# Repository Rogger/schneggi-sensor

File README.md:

# Schneggi sensor 🐌 
A Zigbee sensor integrated with Home Assistant for monitoring temperature, humidity, and optional CO2.

- High accuracy temperature and humidity measurements ([Sensirion SHTC3](https://www.sensirion.com/products/catalog/SHTC3/))
- High accuracy CO2 measurement ([Sensirion SCD40](https://sensirion.com/products/catalog/SCD40)) - optional board
  - CO2 firmware exposes two temperatures: SHTC3 ambient temperature on endpoint 1
    and SCD40 temperature on endpoint 2. The SCD40 reading uses the same sample as
    CO2 and can be affected by self-heating and enclosure conditions; use SHTC3
    as the primary ambient reading. The existing SHTC3 humidity entity is unchanged.
- Low power consumption and long battery life for the non-CO2 variant
  - Hardware: nRF52840 chip, low-current linear regulator, battery monitor with on/off capability 
  - Software: Zigbee sleepy end device for the non-CO2 variant
  - Measured: 3uA average over 1 minute without CO2 (before OTA support)
- The non-CO2 variant can be powered with 3V to 6V (JST connector), e.g. 350mAh li-poly.
- The CO2 variant is USB-C powered. It advertises DC power, keeps its Zigbee receiver on while idle, and does not report a battery.
- Small footprint (3,5cm x 3cm )
- Tested with [Home Assistant](https://www.home-assistant.io/) and [SkyConnect](https://www.home-assistant.io/skyconnect/)

After upgrading CO2 firmware to a build with the second temperature endpoint,
Home Assistant ZHA must discover endpoint 2. Re-interview/reconfigure the device;
if the endpoint list remains cached, remove and pair the device again. Both
temperature entities use the standard Temperature Measurement cluster, so no
custom quirk is required. You can rename them in HA to **Temperature SHTC3** and
**Temperature SCD40**; endpoint 1 is SHTC3 and endpoint 2 is SCD40. The new reading
uses the same sampling interval, 0.1 °C fallback change threshold, daily refresh,
and standard Configure Reporting support as the existing temperature reading.

## Battery power management

The non-CO2 debug and production profiles enable I2C runtime power management.
The application enables it on the sensor bus; the TWIM driver suspends the
controller and applies its sleep pin configuration between transfers.
Polling, sampling intervals, and SHTC3 measurement accuracy are unchanged.

Failed SHTC3 fetches attempt a sleep command after a 13 ms settling delay,
working around the SDK driver's missing error-path cleanup without changing
the shared SDK. Cleanup is best-effort: an inaccessible sensor cannot be forced
to sleep. The original fetch error is retained and no failed sample is reported.
The command and conversion timing follow the
[SHTC3 datasheet](https://sensirion.com/file/datasheet_shtc3).

Battery-profile rejoin delays grow from 1 second exponentially to a one-hour
cap (1, 2, 4, ..., 1024, 2048, 3600 seconds). Successful reconnection resets the
backoff. After prolonged outages, recovery may therefore wait up to an hour
before the next attempt, plus commissioning time. USB-powered CO2 profiles keep
their 15-minute cap and do not enable I2C runtime PM or battery monitoring.

Battery measurements run hourly in debug builds and daily in production builds.
If sampling or updating either battery attribute fails, the firmware retries on
the next sensor cycle (one or ten minutes respectively). A successful update
starts the next battery interval. The firmware attempts to disable the divider
on every path and logs cleanup failures.

The firmware restarts if Zigbee startup or scheduling a required measurement,
rejoin, or watchdog alarm fails, so it cannot stay running indefinitely without
that work. Ordinary join failures still use the rejoin backoff described above.
Alarm replacement removes previous instances and uses overflow-safe conversion
for the full supported sampling range of 1–1440 minutes. Repeated Identify
requests keep one blink alarm; scheduling failure stops the LED animation.

Validate on hardware before relying on battery-life estimates: compare at least
an hour of production-profile current capture before/after, with the debugger
disconnected; check repeated sensor reads, transient I2C failures, and recovery
after a prolonged coordinator outage. Host tests cannot verify physical sleep
current or bus suspend/resume behavior.

## Zigbee reporting

ZHA can configure the standard minimum interval, maximum interval, and
reportable change for endpoint 1's Temperature Measurement (`0x0402`) and
Relative Humidity Measurement (`0x0405`) measured-value (`0x0000`) attributes.
Their changes are in hundredths of a degree Celsius and hundredths of a percent
relative humidity. For settings that differ from ZBOSS's defaults, ZBOSS applies
them to every new sensor reading. Without a configuration, or after reporting
is restored to defaults, the firmware retains its 0.1 °C / 1% change thresholds
and 24-hour refresh. A request for ZBOSS's exact default settings (5-second
minimum, no periodic maximum, zero change) is indistinguishable from a reset
and also uses the firmware fallback.

The CO2 Concentration Measurement (`0x040D`) measured value is refreshed on
every sample, so its Zigbee minimum and maximum reporting intervals can be
configured. ZBOSS treats the single-precision CO2 value as a
changed/unchanged attribute and does not apply a numeric reportable-change
threshold to it. The sensor still samples every minute in debug builds and
every ten minutes in production builds; configuring a shorter reporting
interval does not produce a newer measurement.

## PCB
The PCB was designed with KiCad 7 and manufactured/assembled with JLCPCB. All relevant files can be found in the [repo](hardware)

## HomeAssistant

## Case

## Build
This project uses a **west workspace** (manifest in `west.yml`) and a local Makefile wrapper.
The supported stack is **nRF Connect SDK 3.4.1** with **Zigbee R23 add-on 1.4.0**,
using its R22 behavior mode. SDK and add-on revisions are pinned in `west.yml`;
Zephyr, MCUboot, and other modules come from the SDK manifest. The SCD40 uses
Zephyr's native SCD4X driver. See [migration notes](docs/sdk-upgrade.md).

### 1) One-time workspace setup
Install Nordic's `nrfutil` and the matching toolchain (the Makefile selects the
toolchain associated with this release, rather than the first installed bundle):

```bash
nrfutil install toolchain-manager device
nrfutil toolchain-manager install --ncs-version v3.4.1 --install-dir "$HOME/ncs"
```

From the project directory, initialize the workspace if it does not already exist:

```bash
nrfutil toolchain-manager launch --ncs-version v3.4.1 --install-dir "$HOME/ncs" -- west init -l .
make west-update
```

This initializes a west workspace in the parent directory and fetches all required modules.
For an existing workspace, run `make west-update` with the new toolchain.

The Makefile uses the parent west workspace when `../.west` exists. To use a
different NCS workspace, pass `NCS_WORKSPACE=/path/to/workspace`, or put this
override in the ignored `local.mk`. That workspace must use this checkout's
`west.yml`, including the Zigbee add-on. Builds reject mismatched manifests and
module revisions. An SDK workspace initialized from Nordic's manifest alone
does not include Schneggi's pinned add-on.
Builds compare the cached sysbuild source with the selected NCS workspace and
regenerate incompatible project build directories automatically. West's
automatic pristine mode handles other cache incompatibilities.

### 2) Build
Firmware builds now include signed MCUboot/Zigbee OTA support. Supply
`OTA_SIGNING_KEY=/absolute/private/schneggi.pem` to the build commands below.
For development only, use `OTA_ALLOW_TEST_KEY=ON` to opt into the public SDK key.
See [OTA setup, signing, ZHA configuration, and recovery](docs/ota.md).
Interrupted transfers can resume from the last completed 4 KiB flash page after
retrying Install in Home Assistant, including after a sensor power cycle. The
running firmware must already include resume support.

```bash
cd <project-dir>
make build-debug OTA_ALLOW_TEST_KEY=ON
```

Default output:
- `build_debug/merged.hex`
- `build_debug/schneggi-sensor/zephyr/zephyr.elf`

### Build Profiles

Convenience targets:

- `make build-debug`
  - Debug build without CO2 / SCD4X
- `make build-debug-co2`
  - Debug build with CO2 / SCD4X
- `make build-production`
  - Production build without CO2 / SCD4X
- `make build-production-co2`
  - Production build with CO2 / SCD4X

Equivalent flash targets:

```bash
make flash-debug
make flash-debug-co2
make flash-production
make flash-production-co2
```

For the CO2 production firmware:

```bash
make build-production-co2 OTA_SIGNING_KEY=/absolute/private/schneggi.pem
make flash-production-co2
```

### 3) Test (host unit tests)

```bash
make test
```

The host tests cover reporting thresholds and counter wraparound, battery conversion,
CO2 attribute validation, Zigbee signal handling, OTA behavior for both power profiles,
and rejoin retry/cancellation behavior. They also exercise sensor fetch/read failures,
failed attribute writes, custom reporting and resets, exact fixed-point conversion,
battery ADC/GPIO error cleanup and retry timing, and OTA package validation/index updates.
OTA resume tests simulate resets throughout a download, torn flash writes and
checkpoint commits, corrupted saved data, and maximum-size images.
Runtime tests cover failed startup, alarm exhaustion, cancellation failures,
duplicate reconnect signals, and long scheduling intervals. The Python suite also
checks that PCB rule-check failures prevent manufacturing exports under parallel make.
CI runs them in Debug and Release and builds all four firmware profiles. ADC/GPIO
behavior, network recovery over the radio, and sleep current still require hardware tests.

Version tags also run the [GitHub release workflow](docs/releases.md), which publishes
clearly labeled public-development-key firmware, a ready-to-copy ZHA OTA ZIP,
and checksums after validation. Releases preserve the separate CO2/non-CO2 firmware versions.

`make clean` accepts only `build` or `build_*` directories inside this project.

### 4) Flash

Flash targets use `nrfutil device`, which requires SEGGER J-Link on the host.
Programming erases only flash sectors touched by the firmware, verifies the
result, and resets the sensor. `make erase` still erases the entire chip.

```bash
make flash-debug
```

For a specific J-Link probe:

```bash
make flash-production-co2 SNR=<your_jlink_serial>
```

### Useful overrides

```bash
make build BUILD_DIR=build_custom
make build CONF_FILE=prj_production_no_scd4x.conf OVERLAY='boards/schneggi_sensor.overlay;boards/no_scd4x.overlay'
make build-production-co2 NCS_WORKSPACE=/path/to/workspace
make flash SNR=<your_jlink_serial>
```

### Keep dependencies in sync
After updating `west.yml`:

```bash
make west-update
```

## Resources
- The PCB design was inspired by [Getting Started With nRF52 MCU in a PCB](https://resources.altium.com/p/getting-started-nrf52-mcu-pcb#getting-started-schematics)
- The repos [zigbee-plant-sensor](https://github.com/stanvn/zigbee-plant-sensor) and [b-parasite](https://github.com/rbaron/b-parasite) are a great start
- The [Zephyr SCD4X driver](https://github.com/nrfconnect/sdk-zephyr/tree/ncs-v3.4.1/drivers/sensor/sensirion/scd4x)
- The [nRF Sniffer](https://developer.nordicsemi.com/nRF_Connect_SDK/doc/latest/nrf/protocols/zigbee/tools.html) with [https://www.wireshark.org](Wireshark) is a helpful tool to debug Zigbee communication
- The [ZigBee specification 22 1.0](https://csa-iot.org/wp-content/uploads/2022/01/docs-05-3474-22-0csg-zigbee-specification-1.pdf) and [ZigBee Cluster Library R8](https://zigbeealliance.org/wp-content/uploads/2021/10/07-5123-08-Zigbee-Cluster-Library.pdf)

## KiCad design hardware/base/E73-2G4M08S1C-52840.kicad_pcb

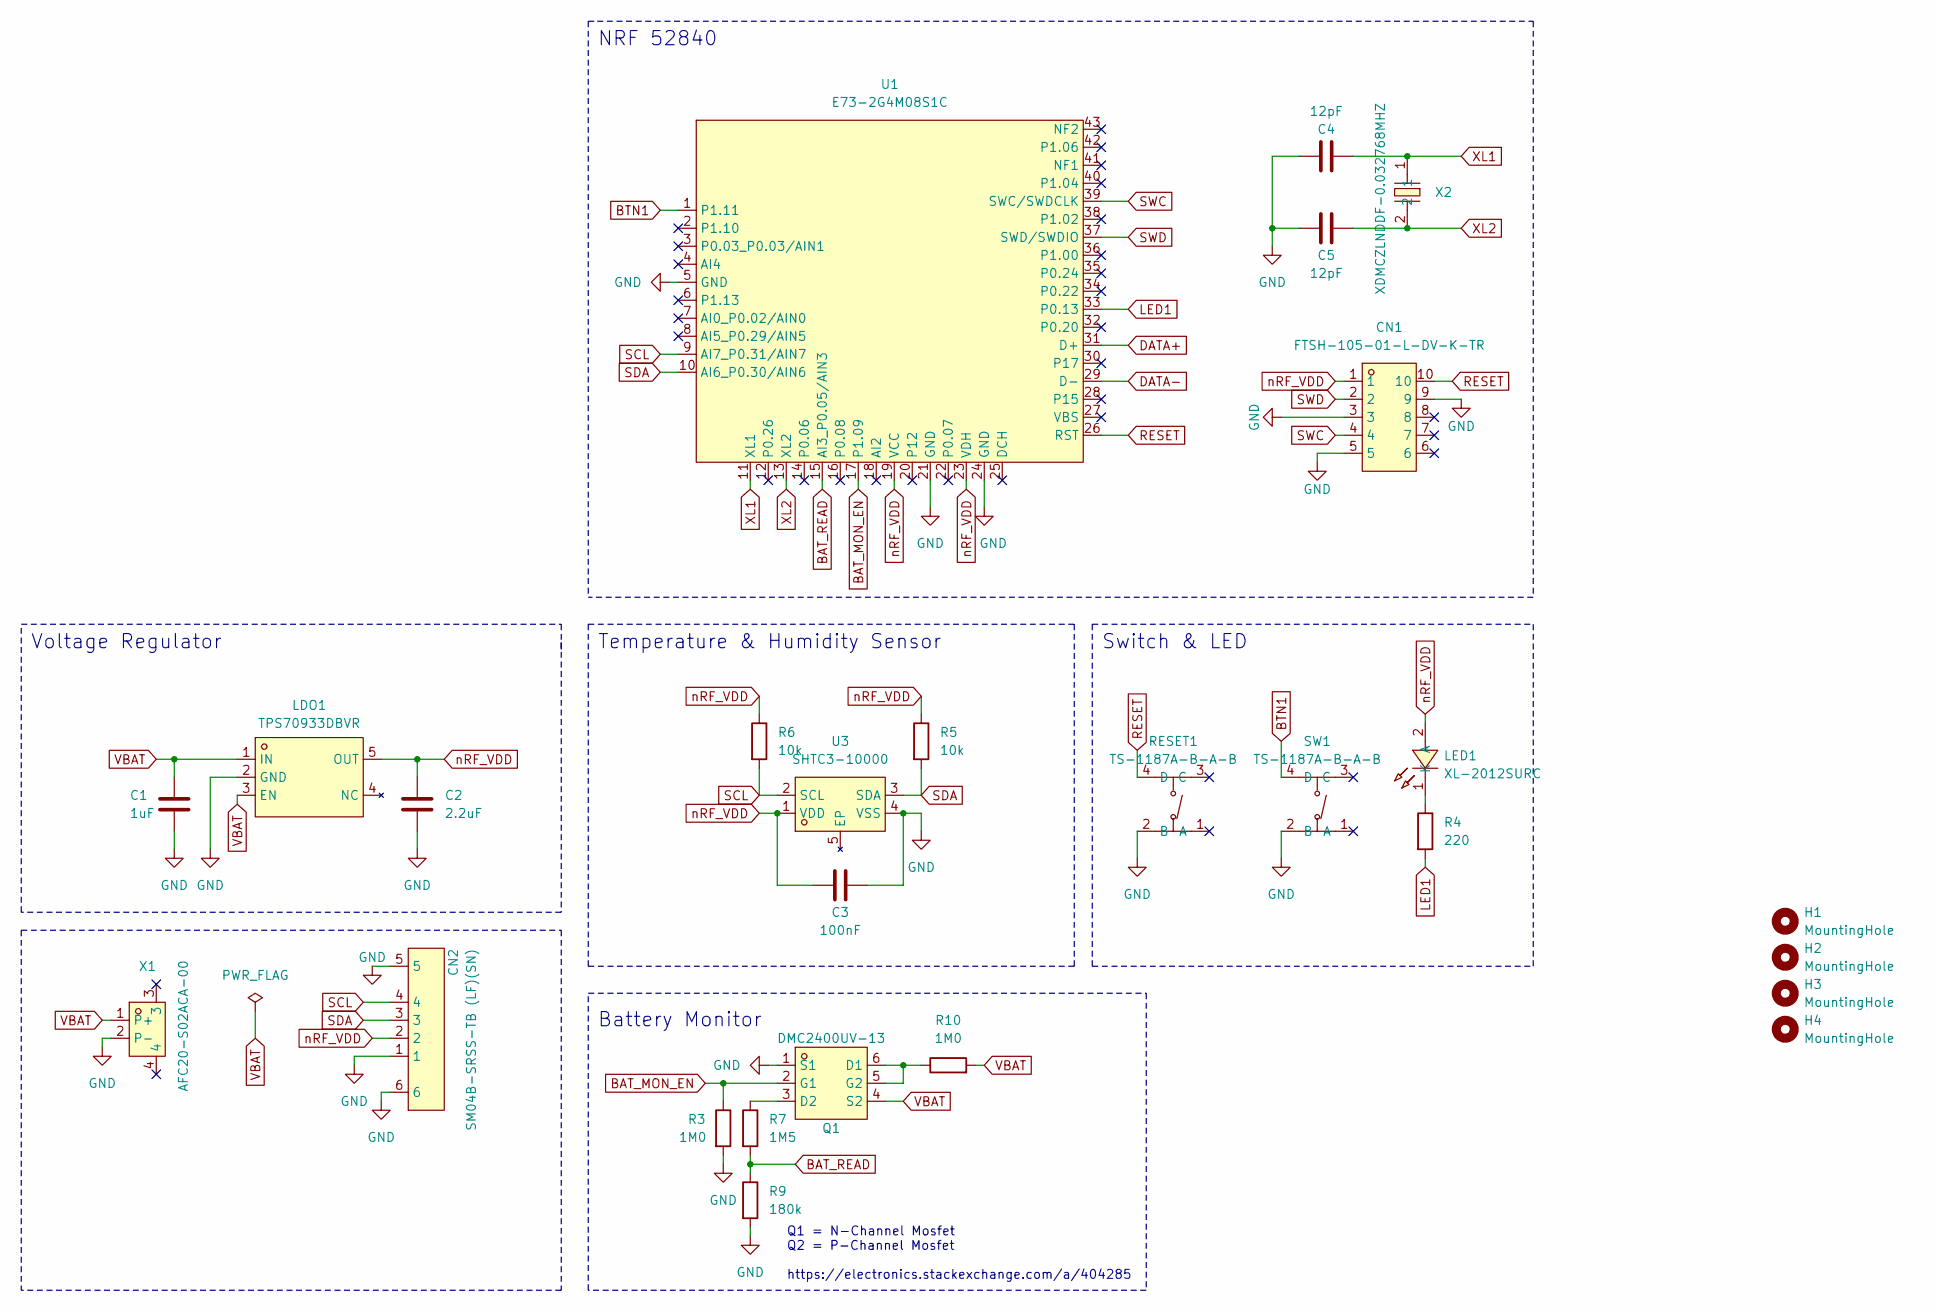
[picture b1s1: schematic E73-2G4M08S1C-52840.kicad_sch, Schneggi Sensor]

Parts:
C1: 1uF; C_0603_1608Metric; LCSC C15849
C2: 2.2uF; C_0603_1608Metric; LCSC C23630
C3: 100nF; C_0603_1608Metric; LCSC C14663
C4, C5: 12pF; C_0603_1608Metric; LCSC C38523
CN1: FTSH-105-01-L-DV-K-TR; CONN-SMD_FTSH-105-01-L-DV-K-TR; LCSC Part C448647
CN2: SM04B-SRSS-TB (LF)(SN); CONN-SMD_4P-P1.00_SM04B-SRSS-TB-LF-SN; LCSC Part C160404
H1, H2, H3, H4: MountingHole; MountingHole_2.2mm_M2
LDO1: TPS70933DBVR; SOT-23-5_L3.0-W1.7-P0.95-LS2.8-BR; LCSC Part C89347
LED1: XL-2012SURC; LED0805-RD_RED; LCSC C84256
Q1: DMC2400UV-13; SOT-563_L1.6-W1.2-P0.50-LS1.6-BL; LCSC Part C500791
R3, R10: 1M0; R_0603_1608Metric; LCSC C22935
R4: 220; R_0603_1608Metric; LCSC C22962
R5, R6: 10k; R_0603_1608Metric; lcsc C98220
R7: 1M5; R_0603_1608Metric; LCSC C4172
R9: 180k; R_0603_1608Metric; LCSC C22827
RESET1: TS-1187A-B-A-B; SW-SMD_4P-L5.1-W5.1-P3.70-LS6.5-TL-2; LCSC Part C318884
SW1: TS-1187A-B-A-B; SW-SMD_4P-L5.1-W5.1-P3.70-LS6.5-TL-2; LCSC Part C318884
U1: E73-2G4M08S1C; WIRELM-SMD_E73-2G4M08S1C; LCSC Part C356849
U3: SHTC3-10000; DFN-4_L2.0-W2.0-P1.00-BL-EP; LCSC Part C2880044
X1: AFC20-S02ACA-00; CONN-SMD_AFC20-S02ACA-00; LCSC Part C2764211
X2: XDMCZLNDDF-0.032768MHZ; CRYSTAL-SMD_L3.2-W1.5-1; LCSC Part C32346

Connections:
BAT_MON_EN: Q1.2 (G1), R3.1, U1.17 (P1.09)
BAT_READ: R7.2, R9.1, U1.15 (AI3_P0.05/AIN3)
BTN1: SW1.4 (D), U1.1 (P1.11)
DATA+: U1.31 (D+)
DATA-: U1.29 (D-)
GND: C1.2, C2.2, C3.2, C4.1, C5.1, CN1.3, CN1.5, CN1.9, CN2.1, CN2.5, CN2.6, LDO1.2 (GND), Q1.1 (S1), R3.2, R9.2, RESET1.2 (B), SW1.2 (B), U1.5 (GND), U1.21 (GND), U1.24 (GND), U3.4 (VSS), X1.2 (P-)
LED1: R4.2, U1.33 (P0.13)
unnamed: LED1.1 (K), R4.1
unnamed: Q1.5 (G2), Q1.6 (D1), R10.1
unnamed: Q1.3 (D2), R7.1
RESET: CN1.10, RESET1.4 (D), U1.26 (RST)
SCL: CN2.4, R6.2, U1.9 (AI7_P0.31/AIN7), U3.2 (SCL)
SDA: CN2.3, R5.2, U1.10 (AI6_P0.30/AIN6), U3.3 (SDA)
SWC: CN1.4, U1.39 (SWC/SWDCLK)
SWD: CN1.2, U1.37 (SWD/SWDIO)
VBAT: C1.1, LDO1.1 (IN), LDO1.3 (EN), Q1.4 (S2), R10.2, X1.1 (P+)
XL1: C4.2, U1.11 (XL1), X2.1
XL2: C5.2, U1.13 (XL2), X2.2
nRF_VDD: C2.1, C3.1, CN1.1, CN2.2, LDO1.5 (OUT), LED1.2 (A), R5.1, R6.1, U1.19 (VCC), U1.23 (VDH), U3.1 (VDD)

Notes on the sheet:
Q1 = N-Channel Mosfet Q2 = P-Channel Mosfet https://electronics.stackexchange.com/a/404285
Temperature & Humidity Sensor
Switch & LED
Voltage Regulator
Battery Monitor
NRF 52840

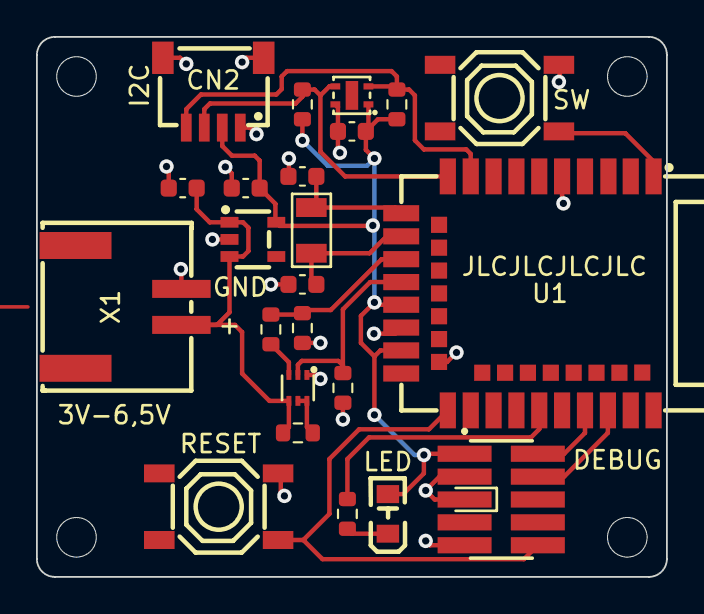
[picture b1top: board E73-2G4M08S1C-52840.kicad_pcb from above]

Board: 2 copper layers, 35.0 x 30.0 mm, 27 parts (0 on the bottom side), 17 nets.

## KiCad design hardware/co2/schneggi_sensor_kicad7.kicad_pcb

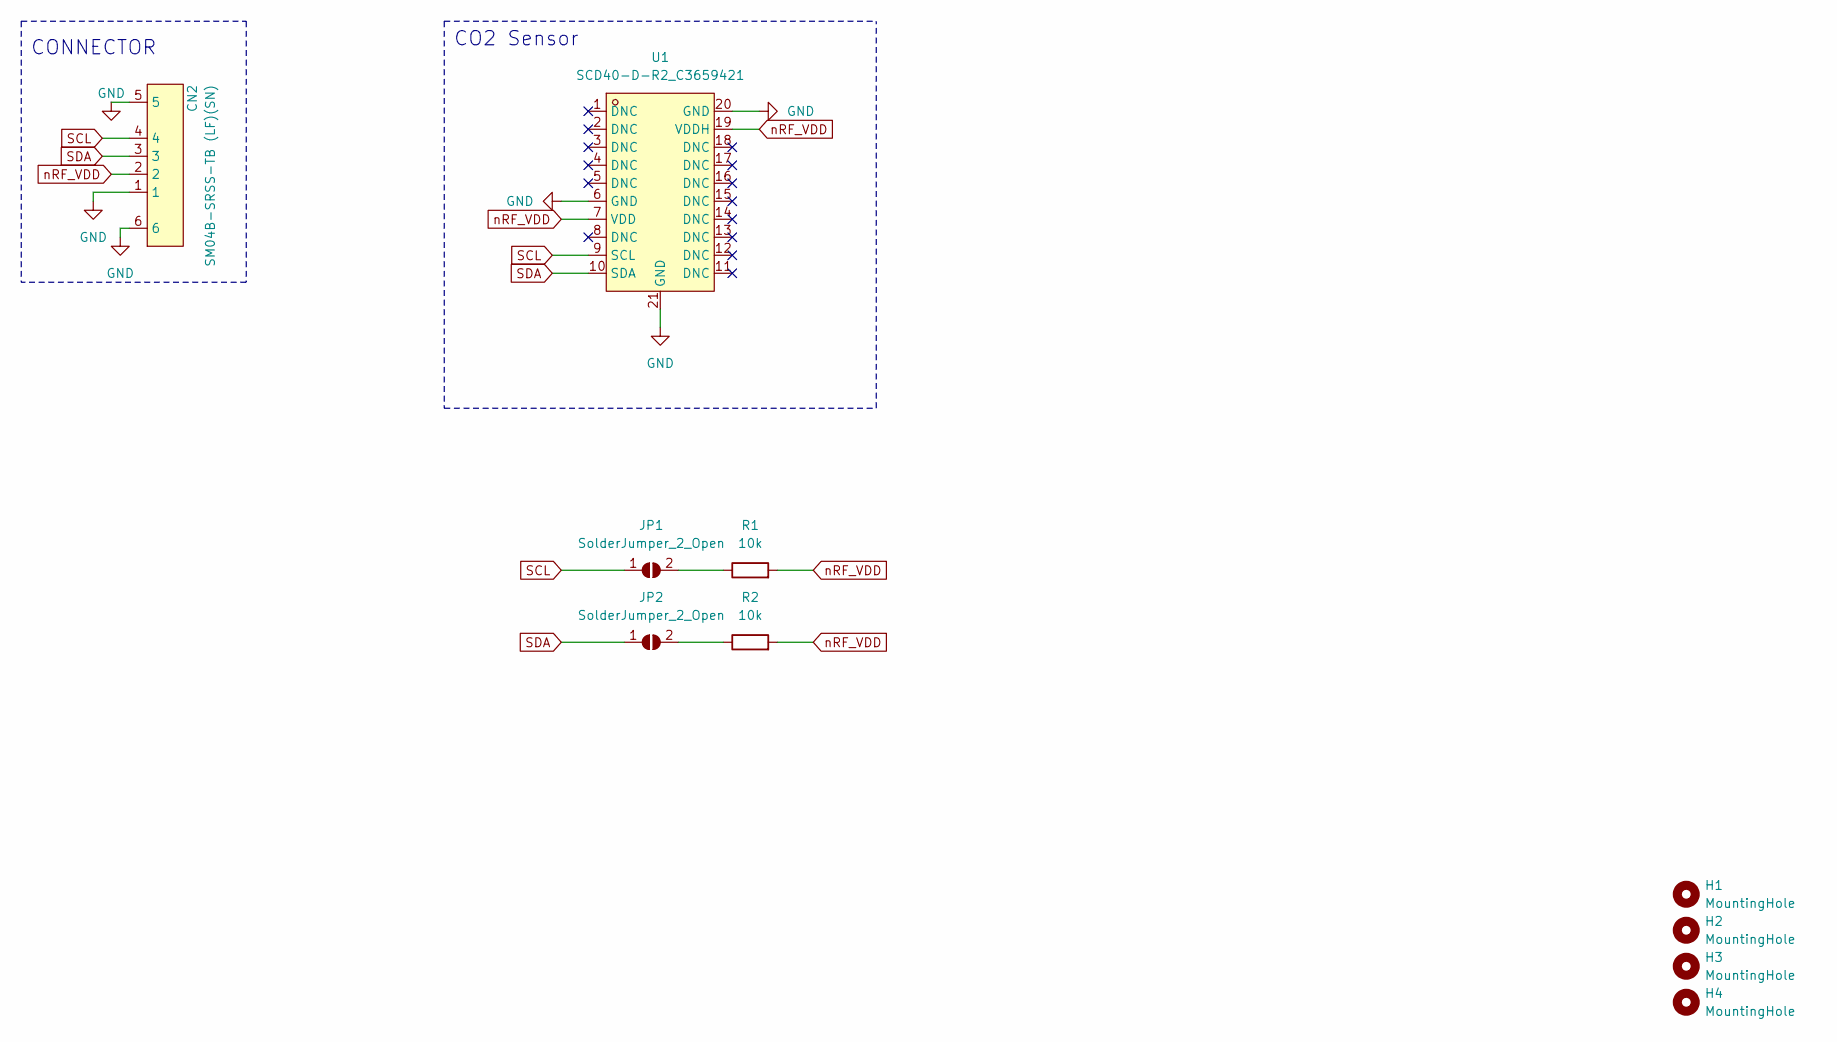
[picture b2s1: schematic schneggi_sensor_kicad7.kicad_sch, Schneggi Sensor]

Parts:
CN2: SM04B-SRSS-TB (LF)(SN); CONN-SMD_4P-P1.00_SM04B-SRSS-TB-LF-SN; LCSC Part C160404
H1, H2, H3, H4: MountingHole; MountingHole_2.2mm_M2
JP1, JP2: SolderJumper_2_Open; SolderJumper-2_P1.3mm_Open_TrianglePad1.0x1.5mm
R1, R2: 10k; R_0603_1608Metric
U1: SCD40-D-R2_C3659421; LGA-20_L10.1-W10.1-P1.25-TL; LCSC Part C3659421

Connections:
GND: CN2.1, CN2.5, CN2.6, U1.6 (GND), U1.20 (GND), U1.21 (GND)
unnamed: JP1.2 (B), R1.1
unnamed: JP2.2 (B), R2.1
SCL: CN2.4, JP1.1 (A), U1.9 (SCL)
SDA: CN2.3, JP2.1 (A), U1.10 (SDA)
nRF_VDD: CN2.2, R1.2, R2.2, U1.7 (VDD), U1.19 (VDDH)

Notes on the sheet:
CO2 Sensor
CONNECTOR

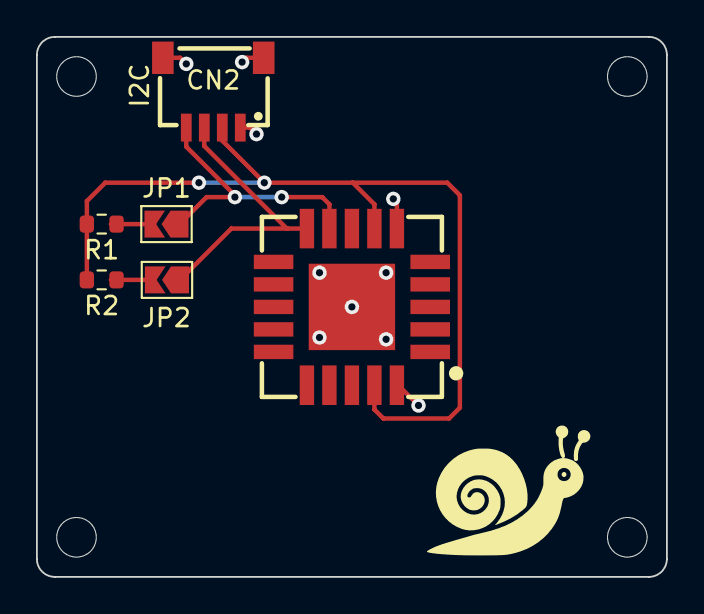
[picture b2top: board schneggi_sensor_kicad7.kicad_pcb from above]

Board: 2 copper layers, 35.0 x 30.0 mm, 10 parts (0 on the bottom side), 6 nets.

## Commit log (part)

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2023-11-21 Initial version
2023-11-21 Add schema pdf
2023-11-21 Fix images in readme
2023-11-21 Optimize for battery life
2023-11-30 Lower power consumption
2023-12-19 Long Poll, Transmit Power
2023-12-20 Fix ZigBee known issue
2024-02-09 Custom Memory, Sleepy End Device
2024-02-09 Set Q size to 128, long poll to 60s, schedule sensor loop after zigbee is intialized
2024-02-16 Remove PWM, Disable UART
2024-02-18 Update README.md for power consumption
2024-07-31 Add CO2 support
2024-07-31 --amend
2024-08-09 Thread status
2024-08-16 Progress
2024-08-16 formatting
2024-08-17 Debug
2024-08-18 Add CI
2024-08-18 Implement zboss handler
2024-08-18 Cleanup
2024-08-29 Add hardware files
2024-08-29 Add V1.1 with CO2 support (#2)
    V1.1
    Smaller outline
    Remove USB-C and physical switch
    Improve signal strength
    Add PH connector for additional sensor boards
    Add CO2 board
2024-09-15 nrf sdk 2.5.2
2024-10-05 Improve broken rejoin
2024-10-05 Add status badge
2024-10-05 Add Kicad files
2024-10-05 Clean
2024-10-05 Add Kicad files for 1.1 (#4)
2024-10-05 Improve broken rejoin (#3)
2025-01-31 Add case stl file
2025-01-31 Add stl files
2025-01-31 Add new Case (#5)
2025-03-22 Add exponetial backoff
2025-06-30 refactor: improve battery level calculation
    The previous implementation of the battery level calculation was inefficient and prone to errors. This commit refactors the `battery_level_pptt` function to use a more robust and efficient algorithm.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
2026-02-08 Fix sensor runtime bugs and concentration cluster typing
2026-02-08 Harden sensor loop and commissioning runtime logic
2026-02-08 Add return-code checks for GPIO, scheduler, and ADC init
2026-02-08 Add simple host logic tests for battery and CO2 helpers
2026-02-08 Make logic test runner auto-detect available C compiler
2026-02-08 Install gcc in CI before running host logic tests
2026-02-08 Expand host logic tests for battery curve and interval math
2026-02-08 Add commissioning state helpers and host transition tests
2026-02-13 Tune sleepy Zigbee defaults for weak RF stability
2026-02-15 Fix Zigbee steering flow and add Makefile tasks
2026-02-15 Add Zigbee signal unit tests and run them in CI
2026-02-15 Add gitignore for local build and KiCad artifacts
2026-02-15 CI: run host unit tests via gcc script in container
2026-02-15 CI: align toolchain container with NCS v2.5.2
2026-02-15 CI: use available NCS 2.5.x toolchain container tag
2026-02-15 Refine Zigbee reboot lifecycle handling and diagnostics
2026-02-18 Keep last Zigbee sensor values when sensors are unavailable
2026-02-18 Fix Zigbee lifecycle handling; add tests/CI and sensor fallback (#11)
    * Fix Zigbee steering flow and add Makefile tasks
    * Add Zigbee signal unit tests and run them in CI
    * Add gitignore for local build and KiCad artifacts
    * CI: run host unit tests via gcc script in container
    * CI: align toolchain container with NCS v2.5.2
    * CI: use available NCS 2.5.x toolchain container tag
2026-02-18 Fix critical Zigbee sensor bugs and harden build workflow
2026-02-18 Fix timing overflow and invalid battery cycle config
2026-02-18 Include ram_pwrdn header to fix implicit declaration
2026-02-18 Fix CO2 cluster SINGLE type compatibility with ZHA
2026-02-22 Fix CO2 concentration SINGLE value semantics
2026-02-22 Add CO2 ZCL semantics helper and unit tests
2026-02-23 Restore CO2 0x040D SINGLE semantics for ZHA reporting (#13)
2026-02-24 Add balanced Zigbee power profile defaults
2026-02-24 Add balanced Zigbee power profile defaults (#14)
2026-02-25 docs: add NCS migration validation checklist
2026-02-25 docs: record blocked hardware validation status for v2.9.2
2026-02-25 ci: use CONF_FILE for debug build config
2026-02-25 docs: log migration step from v2.6.0 to v2.7.0
2026-02-25 build: bump NCS revision to v2.6.0
2026-02-25 ci: align workflow container with NCS v2.9.2
2026-02-25 build: bump NCS revision to v2.9.2
2026-02-25 build: bump NCS revision to v2.7.0
2026-02-25 docs: log migration step from v2.8.0 to v2.9.2
2026-02-25 build: bump NCS revision to v2.8.0
2026-02-25 docs: add NCS migration strategy for Zigbee sensor
2026-02-25 build: drop non-user-configurable SoC symbols from defconfig
2026-02-25 docs: log migration step from v2.5.2 to v2.6.0
2026-02-25 build: remove non-user-configurable BOARD symbol from defconfig
2026-02-25 fix: update SHTCx devicetree for NCS v2.8
2026-02-25 fix: adapt custom concentration attr macros for NCS v2.6 ZBOSS struct
2026-02-25 ci: run co2 tests and drop migration markdown docs
2026-02-25 ci: run all unit tests via cmake and ctest
2026-02-25 test: unify unit suites under top-level cmake/ctest
2026-02-25 ci: force ninja generator for unit test configure
2026-02-26 NCS migration to v2.9.2 with Zigbee/SHTCx compatibility updates (#10)
    * docs: add NCS migration strategy for Zigbee sensor
    * docs: add NCS migration validation checklist
    * build: bump NCS revision to v2.6.0
    * fix: adapt custom concentration attr macros for NCS v2.6 ZBOSS struct
    * docs: log migration step from v2.5.2 to v2.6.0
    * build: bump NCS revision to v2.7.0
2026-02-27 Add SCD4X optional build config and Zigbee startup toggles
2026-02-27 build: switch to pure west workflow and fix flash defaults
2026-02-27 docs: update README for pure west workflow
2026-02-27 Build: switch to pure west workflow (#16)
    * build: switch to pure west workflow and fix flash defaults
    * docs: update README for pure west workflow
2026-02-27 Make SCD4X optional and remove CO2 cluster when disabled
2026-03-01 Make SCD4X optional and remove CO2 cluster when disabled (#17)
2026-03-06 Fix battery reporting cadence rounding
2026-03-15 Optimize battery-powered sensor reporting
2026-03-21 Fix stale Zigbee attribute values
2026-03-22 Optimize battery-powered sensor reporting (#18)
    * Fix battery reporting cadence rounding
    * Optimize battery-powered sensor reporting
    * Fix stale Zigbee attribute values
2026-04-17 Improve Zigbee rejoin recovery and build targets
2026-04-17 Ignore local build and Codex artifacts
2026-04-17 Fix Zigbee long poll interval units
2026-04-17 Avoid forced steering on parent link failure
2026-04-17 Add unit coverage for rejoin state machine
2026-04-19 Improve Zigbee rejoin recovery and build targets (#19)
    * Improve Zigbee rejoin recovery and build targets
    * Ignore local build and Codex artifacts
    * Fix Zigbee long poll interval units
    * Avoid forced steering on parent link failure
    * Add unit coverage for rejoin state machine
2026-05-03 Add flash adapter PCB production files
2026-05-06 Add flash adapter silkscreen logo
2026-06-28 Fix CO2 firmware workspace setup
2026-06-29 Disable unused QSPI flash node
